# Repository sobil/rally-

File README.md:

# Rally-
_Pronounced "Rally Dash"_

This code is designed to be used as a trip computer, speedo, odometer.

Presently it simply implements twin independent odometers using the internal clock on the atmel chip.

The code was designed for use on a micro arduino using a SPI driven 240X128 LCD graphical display and a hall sensor. Unlike many other examples this code uses the internal counter on the CPU and should be more reliable than other interrupt and pin check loop methods.

PRs and issues welcome. I plan to include more hardware details in time.

## Parts List

Noteable:
- *LCD:* https://www.buydisplay.com/serial-graphic-module-display-240x128-cog-with-uc1608-controller
- *HALL sensor:* A3144 Sensor https://components101.com/sensors/a3144-hall-effect-sensor
- *CONNECTORS:* JST PH2.0  (2Pin 3Pin 4Pin 5Pin)
- *BUTTONS:* https://www.jaycar.com.au/ip67-rated-dome-pushbutton-switch-black/p/SP0656

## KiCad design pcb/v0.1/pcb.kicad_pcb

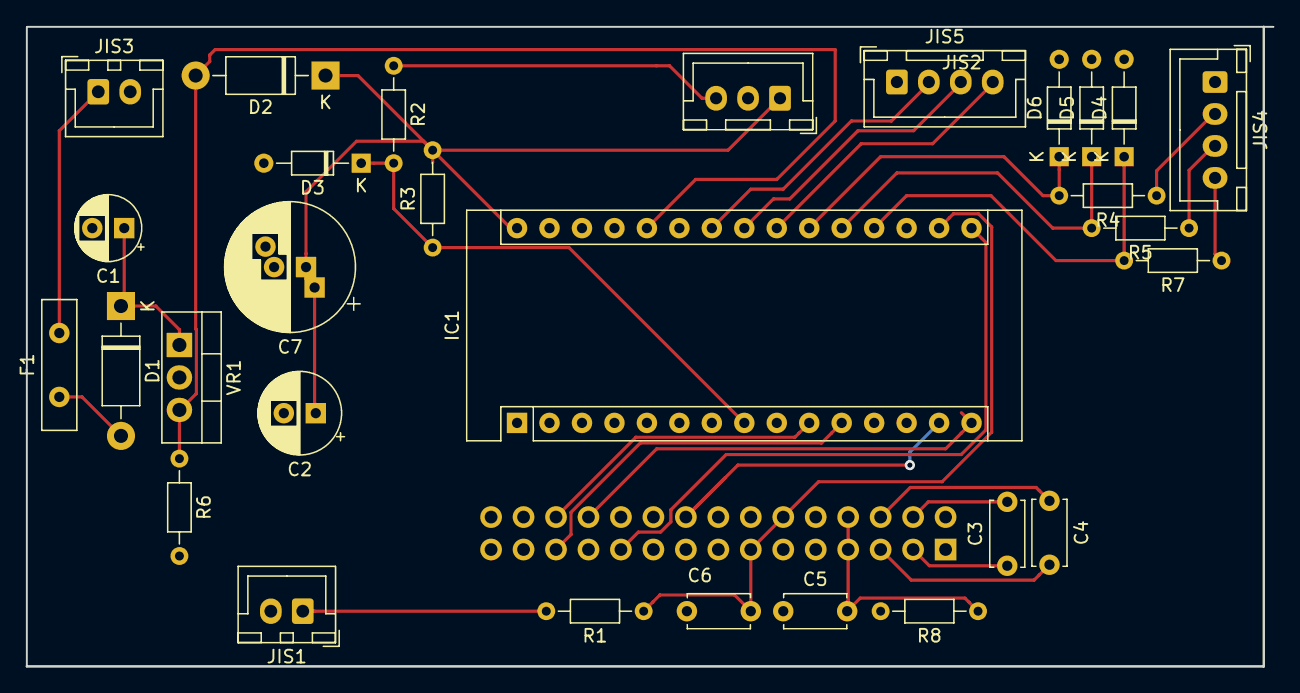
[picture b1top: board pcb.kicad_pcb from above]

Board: 2 copper layers, 97.5 x 50.0 mm, 30 parts (1 on the bottom side), 29 nets.

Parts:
C1: 200uF; CP_Radial_D5.0mm_P2.50mm
C2: 100uF; CP_Radial_D6.3mm_P2.50mm
C3, C4: 4.7uF; C_Disc_D5.0mm_W2.5mm_P5.00mm
C5, C6: 0.1uF; C_Disc_D4.7mm_W2.5mm_P5.00mm
C7: 5.5V 0.47F; CP_Radial_D10.0mm_P2.50mm_P5.00mm
D1: 1N4007; D_DO-41_SOD81_P10.16mm_Horizontal
D2: 1N4001; D_DO-41_SOD81_P10.16mm_Horizontal
D3, D4, D5, D6: D_Zener_Small; D_DO-34_SOD68_P7.62mm_Horizontal
Display1: LCD; PinHeader_2x15_P2.54mm_Vertical
F1: Polyfuse 500ma 60V; C_Disc_D10.0mm_W2.5mm_P5.00mm
IC1: Nano_v3.x; Arduino_Nano
JIS1: LCD_BL; JST_XH_B02B-XH-A_1x02_P2.50mm_Vertical
JIS2: Speedo Connector; JST_XH_B03B-XH-A_1x03_P2.50mm_Vertical
JIS3: Power Connector; JST_XH_B02B-XH-A_1x02_P2.50mm_Vertical
JIS4: external button connector; JST_XH_B04B-XH-A_1x04_P2.50mm_Vertical
JIS5: int key; JST_XH_B04B-XH-A_1x04_P2.50mm_Vertical
R1: R4.3; R_Axial_DIN0204_L3.6mm_D1.6mm_P7.62mm_Horizontal
R2, R4, R5, R7: R100; R_Axial_DIN0204_L3.6mm_D1.6mm_P7.62mm_Horizontal
R3, R6: R10K; R_Axial_DIN0204_L3.6mm_D1.6mm_P7.62mm_Horizontal
R8: 10M; R_Axial_DIN0204_L3.6mm_D1.6mm_P7.62mm_Horizontal
VR1: LM7805_TO220; TO-220-3_Vertical

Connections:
+3V3: C6.2, Display1.12, Display1.13, IC1.17, R1.1
+5V: C2.1, C7.1, D2.1, IC1.30, JIS2.1, R3.2
+BATT: F1.2, JIS3.1
GND: C1.2, C2.2, C5.1, C6.1, C7.2, D3.2, D4.2, D5.2, D6.2, Display1.2, Display1.10, Display1.11, Display1.16, Display1.19, Display1.20, Display1.23, Display1.27, Display1.28, Display1.29, IC1.4, IC1.29, JIS1.2, JIS2.2, JIS3.2, JIS4.1, JIS5.1, R6.2, R8.2, VR1.2
unnamed: C1.1, D1.1, VR1.1
unnamed: C3.1, Display1.3
unnamed: C3.2, Display1.4
unnamed: C4.1, Display1.6
unnamed: C4.2, Display1.5
unnamed: C5.2, Display1.7, Display1.8, R8.1
unnamed: D1.2, F1.1
unnamed: D2.2, IC1.26, R6.1, VR1.3
unnamed: D3.1, IC1.8, R2.2, R3.1
unnamed: D4.1, IC1.19, R7.2
unnamed: D5.1, IC1.20, R5.2
unnamed: D6.1, IC1.21, R4.2
unnamed: Display1.18, IC1.14
unnamed: Display1.21, IC1.16
unnamed: Display1.24, IC1.15
unnamed: Display1.25, IC1.11
unnamed: Display1.26, IC1.10
unnamed: IC1.22, JIS5.4
unnamed: IC1.23, JIS5.3
unnamed: IC1.24, JIS5.2
unnamed: JIS1.1, R1.2
unnamed: JIS2.3, R2.1
unnamed: JIS4.2, R4.1
unnamed: JIS4.3, R5.1
unnamed: JIS4.4, R7.1

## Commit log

2020-07-16 update PCB
2020-07-16 gitignore update
2020-07-23 v0.1-r2
2021-09-05 scadfile between circuit board and screen
2021-09-05 removing comments
2021-09-07 update: Enclosure WIP
2021-09-07 WIP: Initial concept kick off
2021-09-11 add enclosure back
2021-09-19 Add some parts links
